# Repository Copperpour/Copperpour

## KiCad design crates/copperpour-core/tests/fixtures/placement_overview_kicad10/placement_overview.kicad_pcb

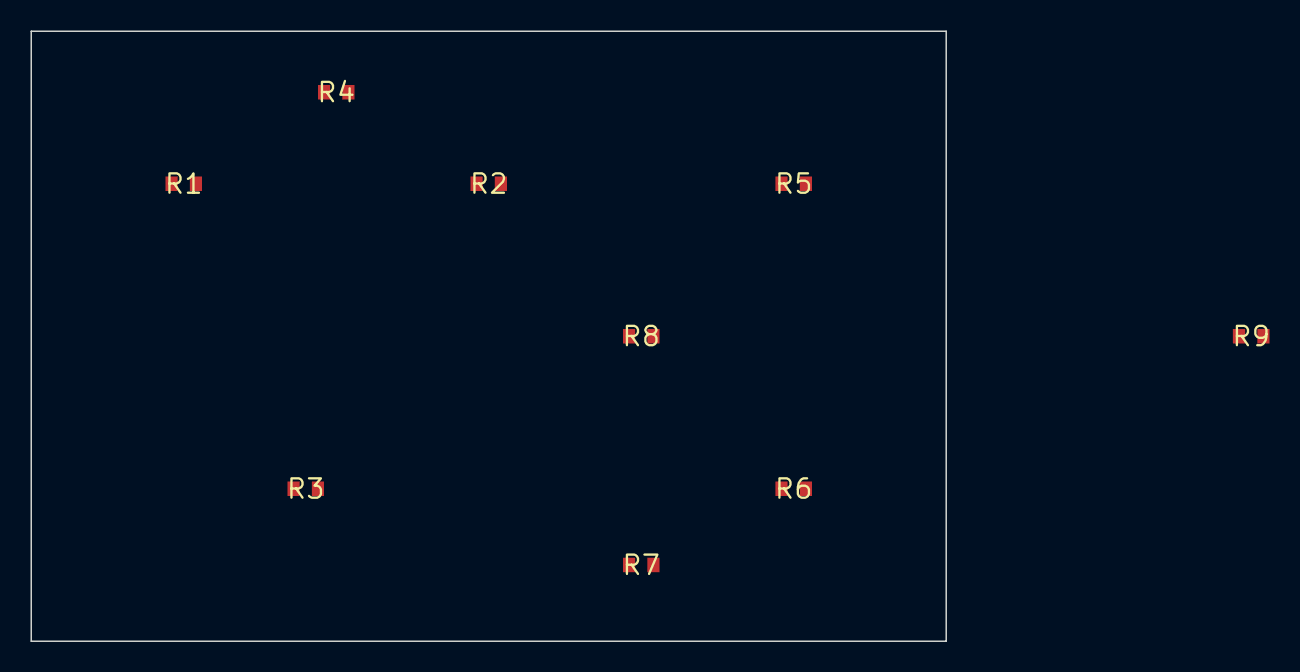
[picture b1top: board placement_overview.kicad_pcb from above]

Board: 2 copper layers, 60.0 x 40.0 mm, 9 parts (0 on the bottom side), 7 nets, no tracks yet.

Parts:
R1, R2, R3, R4, R5, R6, R7, R8, R9: 10k; R_0603

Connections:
/drv/HV_OUT: R7.2, R8.1
/power/VCC: R4.2, R5.2
GND: R1.2, R2.2, R8.2, R9.2
HV: R6.2, R7.1
SIG_A: R1.1, R2.1, R3.1
SIG_B: R3.2, R4.1, R9.1
VCC: R5.1, R6.1

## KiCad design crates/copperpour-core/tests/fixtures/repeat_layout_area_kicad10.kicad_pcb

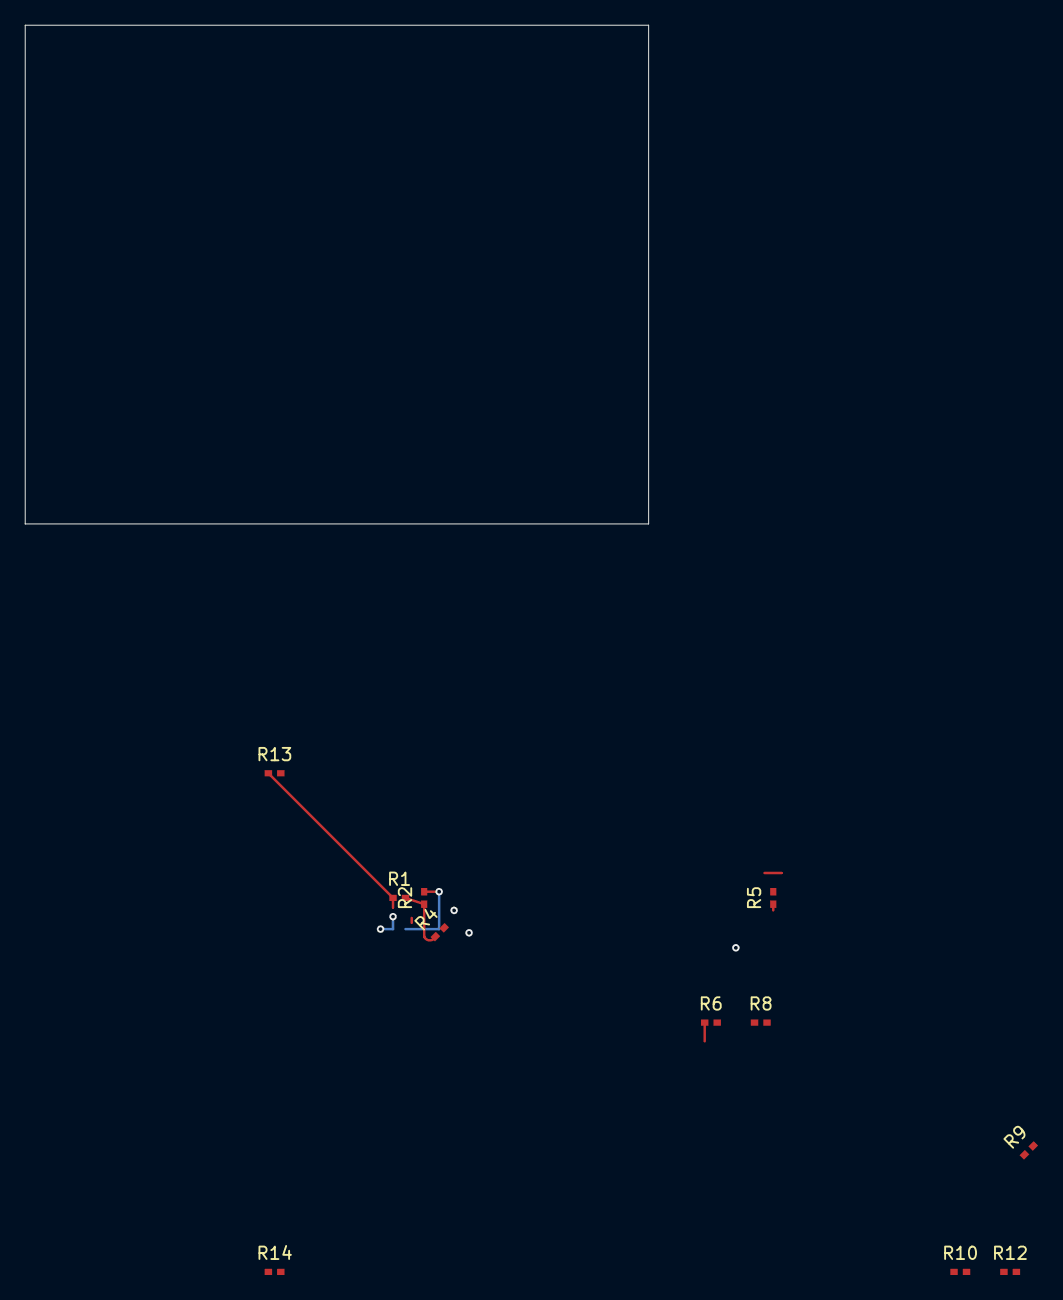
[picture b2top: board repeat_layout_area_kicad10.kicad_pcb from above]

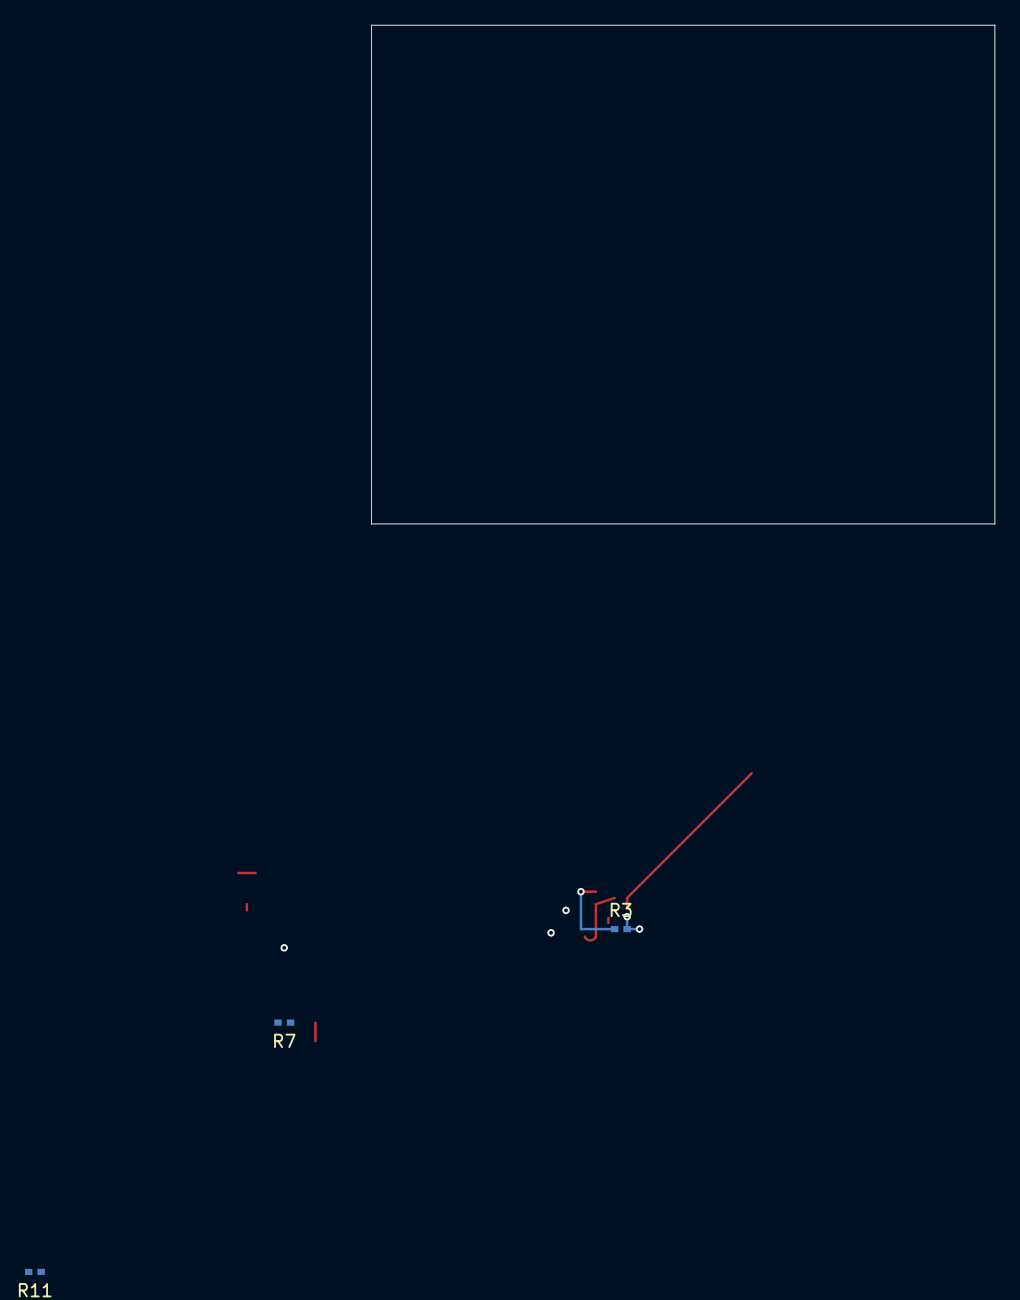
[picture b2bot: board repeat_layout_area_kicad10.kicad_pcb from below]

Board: 2 copper layers, 50.0 x 40.0 mm, 14 parts (3 on the bottom side), 8 nets.

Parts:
R1, R2, R3, R4, R5, R6, R7, R8, R9, R10, R11, R12, R13, R14: 10k; R_0402

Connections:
/Channel 1/IN: R1.1, R13.1
/Channel 1/MID: R1.2, R2.1, R4.1
/Channel 1/OUT: R2.2, R3.1
/Channel 2/MID: R5.2, R6.1, R8.1
/Channel 2/OUT: R6.2, R7.1
/Channel 3/MID: R9.2, R10.1, R12.1
/Channel 3/OUT: R10.2, R11.1
GND: R3.2, R4.2, R7.2, R8.2, R11.2, R12.2, R13.2, R14.2
